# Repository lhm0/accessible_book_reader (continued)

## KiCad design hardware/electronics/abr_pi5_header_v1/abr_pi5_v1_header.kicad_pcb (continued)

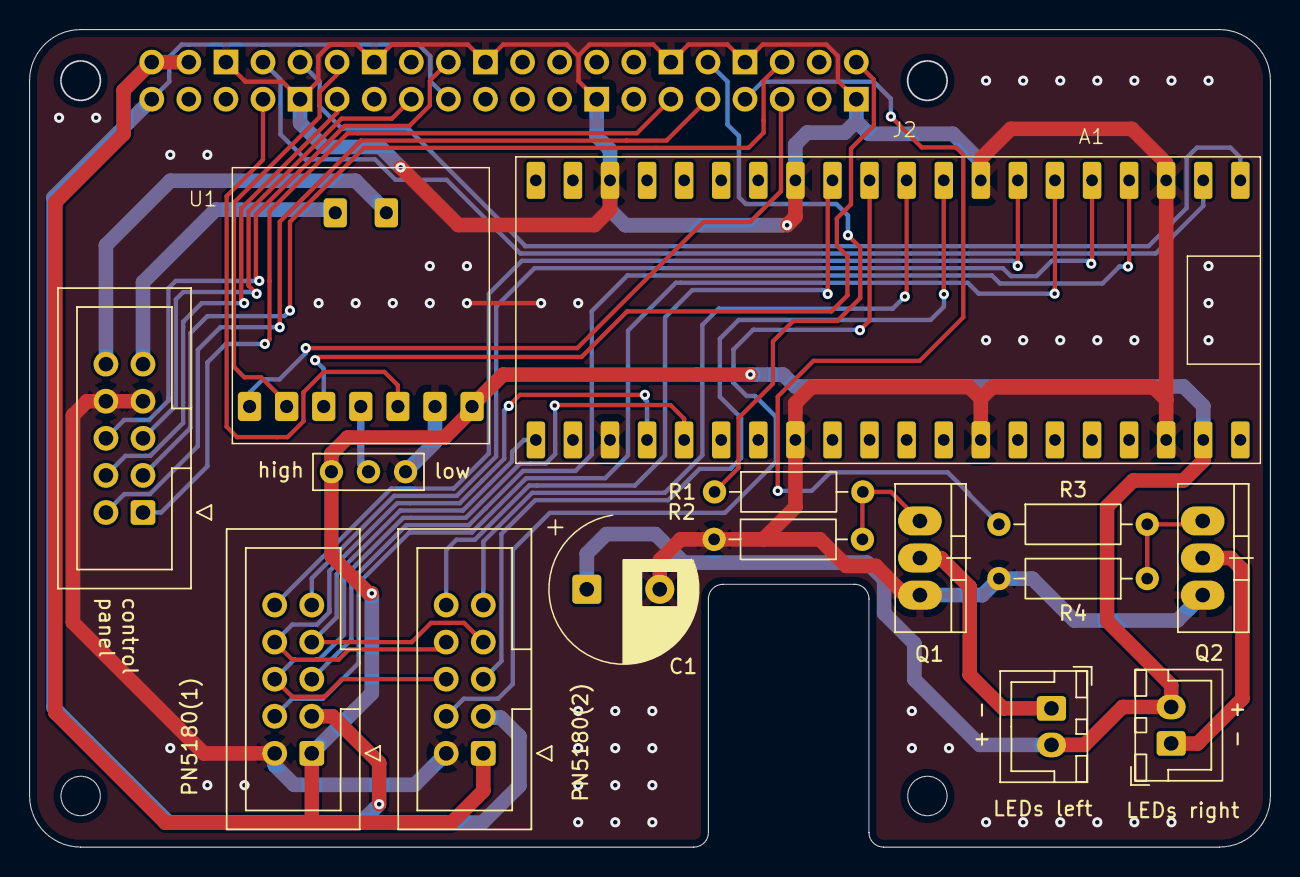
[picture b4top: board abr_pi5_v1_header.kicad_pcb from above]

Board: 2 copper layers, 85.0 x 56.0 mm, 16 parts (0 on the bottom side), 35 nets.

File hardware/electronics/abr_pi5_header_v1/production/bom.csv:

Designator,Footprint,Quantity,Value,LCSC Part #
A1,RaspberryPiPico,1,SC0918,
C1,CP_Radial_D10.0mm_P5.00mm_slim_silkscreen,1,470µ,
J1,3_pin_jumper,1,Conn_01x03_Pin,
J2,RPI_HAT_back,1,RPi_GPIO,
"J4, J5, J6",IDC-Header_2x05_P2.54mm_Vertical_centered,3,10 pin IDC connector,
J7,JST_XH_B2B-XH-A_1x02_P2.50mm_Vertical,1,LED_left,
J8,JST_XH_B2B-XH-A_1x02_P2.50mm_Vertical,1,LED_right,
"Q1, Q2",TO220_vertikal,2,FQP30N06L,
"R1, R3",R_Axial_DIN0207_L6.3mm_D2.5mm_P10.16mm_Horizontal,2,100,
"R2, R4",R_Axial_DIN0207_L6.3mm_D2.5mm_P10.16mm_Horizontal,2,100k,
U1,MAX98357A_breakout,1,MAX98357A,

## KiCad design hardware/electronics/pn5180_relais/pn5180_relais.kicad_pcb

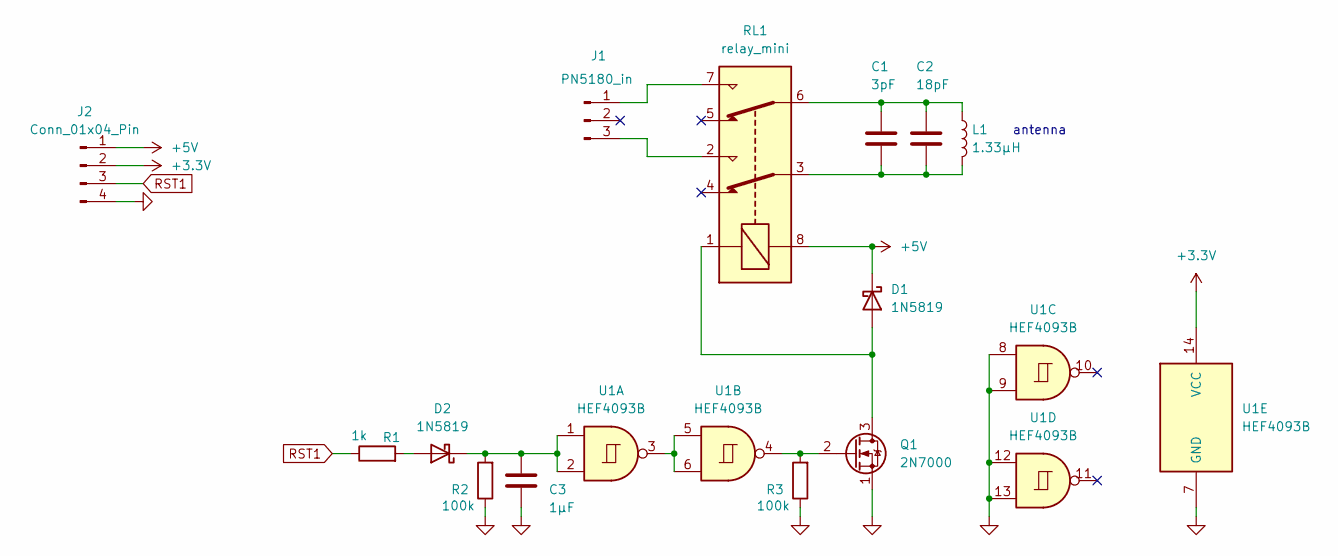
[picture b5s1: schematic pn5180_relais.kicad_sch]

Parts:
C1: 3pF; C_aux; LCSC C1653
C2: 18pF; C_aux; LCSC C1653
C3: 1µF; CP_Radial_D4.0mm_P1.50mm
D1, D2: 1N5819; D_A-405_P7.62mm_Horizontal; LCSC C191023
J1: PN5180_in; 3_pin_hori
J2: Conn_01x04_Pin; 4_pin
L1: 1.33µH; NFC_antenna
Q1: 2N7000; TO-92_Inline
R1: 1k; R_Axial_DIN0207_L6.3mm_D2.5mm_P10.16mm_Horizontal
R2, R3: 100k; R_Axial_DIN0207_L6.3mm_D2.5mm_P10.16mm_Horizontal
RL1: relay_mini; Relay
U1: HEF4093B; DIP-14_W7.62mm; LCSC C5456626

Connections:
+3.3V: J2.2, U1.14 (VCC)
+5V: D1.1 (K), J2.1, RL1.8
GND: C3.2, J2.4, Q1.1 (S), R2.1, R3.1, U1.7 (GND), U1.8, U1.9, U1.12, U1.13
unnamed: C1.1, C2.1, L1.2, RL1.3
unnamed: C1.2, C2.2, L1.1, RL1.6
unnamed: D1.2 (A), Q1.3 (D), RL1.1
unnamed: D2.2 (A), R1.2
unnamed: C3.1, D2.1 (K), R2.2, U1.1, U1.2
unnamed: J1.1, RL1.7
unnamed: J1.3, RL1.2
unnamed: Q1.2 (G), R3.2, U1.4
unnamed: U1.3, U1.5, U1.6
RST1: J2.3, R1.1

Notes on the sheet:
antenna

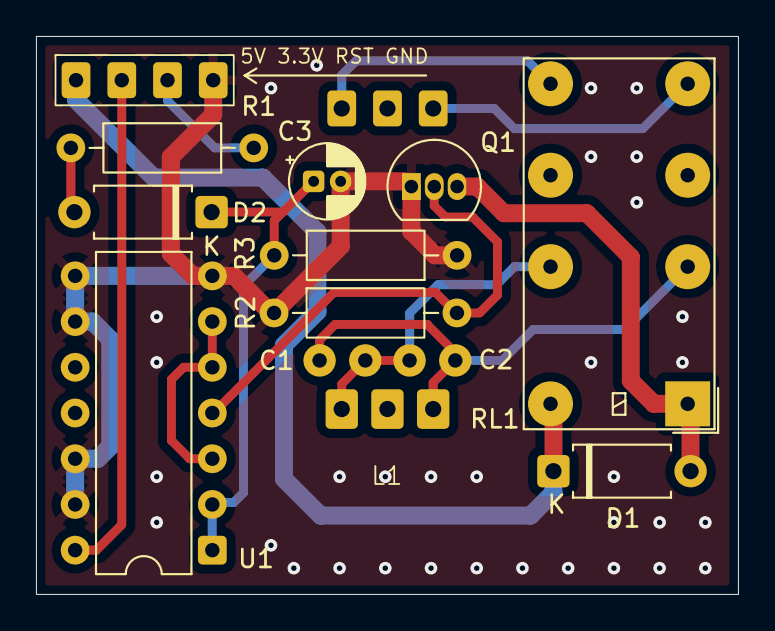
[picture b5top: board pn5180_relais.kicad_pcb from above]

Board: 2 copper layers, 39.0 x 31.0 mm, 14 parts (1 on the bottom side), 13 nets.

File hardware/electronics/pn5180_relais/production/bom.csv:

Designator,Footprint,Quantity,Value,LCSC Part #
C1,C_aux,1,3pF,C1653
C2,C_aux,1,18pF,C1653
C3,CP_Radial_D4.0mm_P1.50mm,1,10µF,
"D1, D2",D_A-405_P7.62mm_Horizontal,2,1N5819,C191023
J1,3_pin_hori,1,PN5180_in,
J2,4_pin,1,Conn_01x04_Pin,
L1,NFC_antenna,1,1.33µH,
Q1,TO-92_Inline,1,2N7000,
R1,R_Axial_DIN0207_L6.3mm_D2.5mm_P10.16mm_Horizontal,1,1k,
"R2, R3",R_Axial_DIN0207_L6.3mm_D2.5mm_P10.16mm_Horizontal,2,100k,
RL1,Relay,1,relay_mini,
U1,DIP-14_W7.62mm,1,HEF4093B,C5456626

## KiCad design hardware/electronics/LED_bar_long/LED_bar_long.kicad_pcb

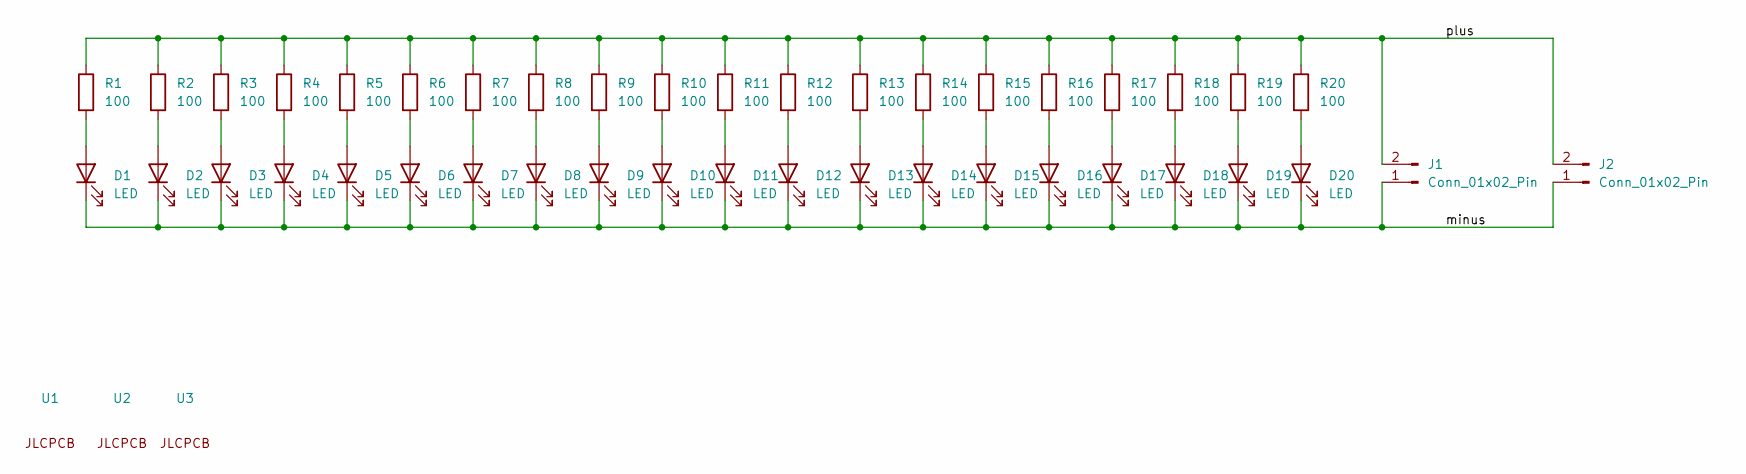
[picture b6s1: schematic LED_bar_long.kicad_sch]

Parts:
D1, D2, D3, D4, D5, D6, D7, D8, D9, D10, D11, D12, D13, D14, D15, D16, D17, D18, D19, D20: LED; LED_1206; LCSC C219234
J1, J2: Conn_01x02_Pin; 2_pin
R1, R2, R3, R4, R5, R6, R7, R8, R9, R10, R11, R12, R13, R14, R15, R16, R17, R18, R19, R20: 100; R_1206_3216Metric; LCSC C17901
U1, U2, U3: JLC_tooling_hole

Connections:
/minus: D1.1 (K), D2.1 (K), D3.1 (K), D4.1 (K), D5.1 (K), D6.1 (K), D7.1 (K), D8.1 (K), D9.1 (K), D10.1 (K), D11.1 (K), D12.1 (K), D13.1 (K), D14.1 (K), D15.1 (K), D16.1 (K), D17.1 (K), D18.1 (K), D19.1 (K), D20.1 (K), J1.1, J2.1
/plus: J1.2, J2.2, R1.1, R2.1, R3.1, R4.1, R5.1, R6.1, R7.1, R8.1, R9.1, R10.1, R11.1, R12.1, R13.1, R14.1, R15.1, R16.1, R17.1, R18.1, R19.1, R20.1
unnamed: D1.2 (A), R1.2
unnamed: D2.2 (A), R2.2
unnamed: D3.2 (A), R3.2
unnamed: D4.2 (A), R4.2
unnamed: D5.2 (A), R5.2
unnamed: D6.2 (A), R6.2
unnamed: D7.2 (A), R7.2
unnamed: D8.2 (A), R8.2
unnamed: D9.2 (A), R9.2
unnamed: D10.2 (A), R10.2
unnamed: D11.2 (A), R11.2
unnamed: D12.2 (A), R12.2
unnamed: D13.2 (A), R13.2
unnamed: D14.2 (A), R14.2
unnamed: D15.2 (A), R15.2
unnamed: D16.2 (A), R16.2
unnamed: D17.2 (A), R17.2
unnamed: D18.2 (A), R18.2
unnamed: D19.2 (A), R19.2
unnamed: D20.2 (A), R20.2

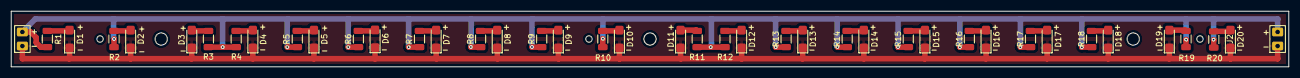
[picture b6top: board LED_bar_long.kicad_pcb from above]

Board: 2 copper layers, 230.0 x 10.0 mm, 45 parts (0 on the bottom side), 22 nets.

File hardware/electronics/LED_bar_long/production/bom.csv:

Designator,Footprint,Quantity,Value,LCSC Part #
"D1, D10, D11, D12, D13, D14, D15, D16, D17, D18, D19, D2, D20, D3, D4, D5, D6, D7, D8, D9",LED_1206,20,LED,C219234
"J1, J2",2_pin,2,Conn_01x02_Pin,
"R1, R10, R11, R12, R13, R14, R15, R16, R17, R18, R19, R2, R20, R3, R4, R5, R6, R7, R8, R9",1206,20,100,C17901
"U1, U2, U3",JLC_tooling_hole,3,~,
